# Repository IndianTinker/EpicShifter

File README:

This is a generic test board for using ULN2803 and 74HC595 Shift Registers.
Useful while testing LED Displays or getting used to new micros :D

It has seperate power pins for darlington and shiftregisters.

If you drive an LED Display using it. Use Shift Register for posiive drive
and ULN2803 for negative drive.

You may need to add pnp transistor for +ve side since the source limit on 595 
is less. In that case you have to invert logic as well.

Hope its useful

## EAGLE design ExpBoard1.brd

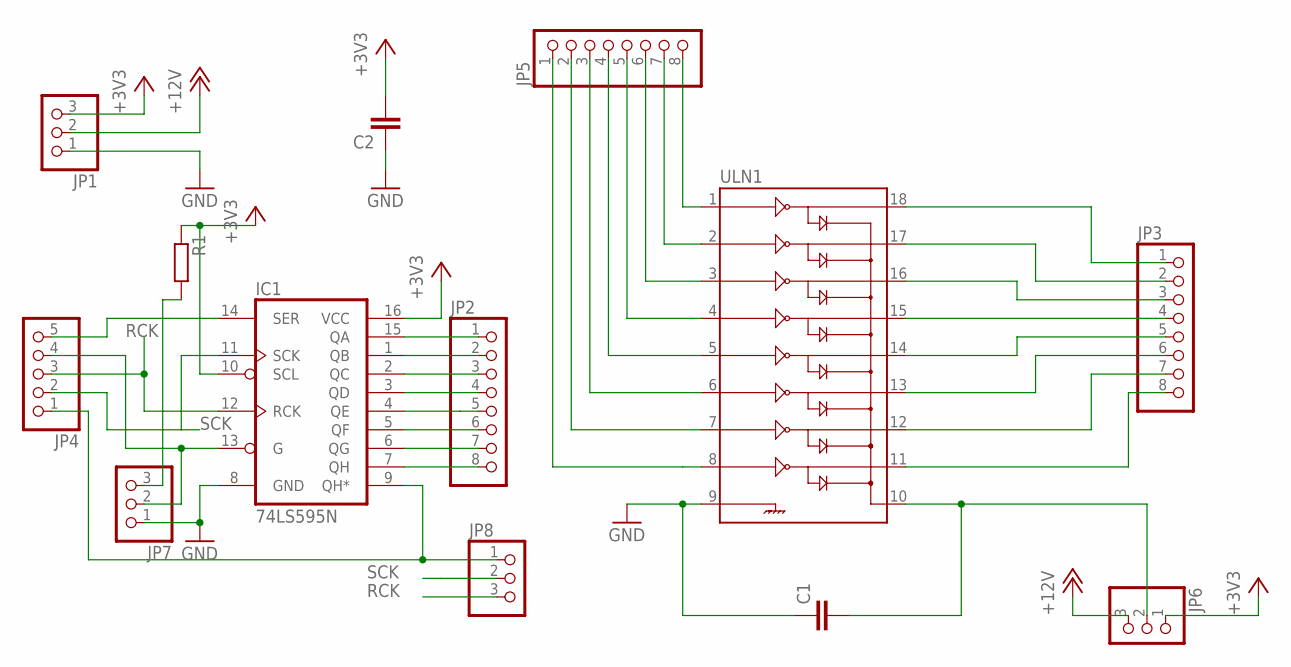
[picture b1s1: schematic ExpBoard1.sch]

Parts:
C1: C-EU050-024X044; C050-024X044
C2: C-EU025-024X044; C025-024X044
IC1: 74LS595N; DIL16
JP1, JP6, JP7, JP8: PINHD-1X3; 1X03
JP2, JP3, JP5: PINHD-1X8; 1X08
JP4: PINHD-1X5; 1X05
R1: R-EU_0207/12; 0207/12
ULN1: ULN2803DIP; DIL18

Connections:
+3V3: C2.2, IC1.10 (SCL), IC1.16 (VCC), JP1.3, JP6.1, R1.1
+12V: JP1.2, JP6.3
GND: C1.1, C2.1, IC1.8 (GND), JP1.1, JP7.1, ULN1.9
unnamed: IC1.14 (SER), JP4.5
unnamed: C1.2, JP6.2, ULN1.10
unnamed: JP3.1, ULN1.18
unnamed: JP3.2, ULN1.17
unnamed: JP3.3, ULN1.16
unnamed: JP3.4, ULN1.15
unnamed: JP3.5, ULN1.14
unnamed: JP3.6, ULN1.13
unnamed: JP3.7, ULN1.12
unnamed: JP3.8, ULN1.11
unnamed: JP5.8, ULN1.1
unnamed: JP5.7, ULN1.2
unnamed: JP5.6, ULN1.3
unnamed: JP5.5, ULN1.4
unnamed: JP5.4, ULN1.5
unnamed: JP5.3, ULN1.6
unnamed: JP5.2, ULN1.7
unnamed: JP5.1, ULN1.8
unnamed: IC1.15 (QA), JP2.1
unnamed: IC1.1 (QB), JP2.2
unnamed: IC1.2 (QC), JP2.3
unnamed: IC1.3 (QD), JP2.4
unnamed: IC1.4 (QE), JP2.5
unnamed: IC1.5 (QF), JP2.6
unnamed: IC1.6 (QG), JP2.7
unnamed: IC1.7 (QH), JP2.8
unnamed: IC1.13 (G), JP4.4, JP7.2
unnamed: IC1.9 (QH*), JP4.1, JP8.1
unnamed: JP7.3, R1.2
RCK: IC1.12 (RCK), JP4.3, JP8.3
SCK: IC1.11 (SCK), JP4.2, JP8.2

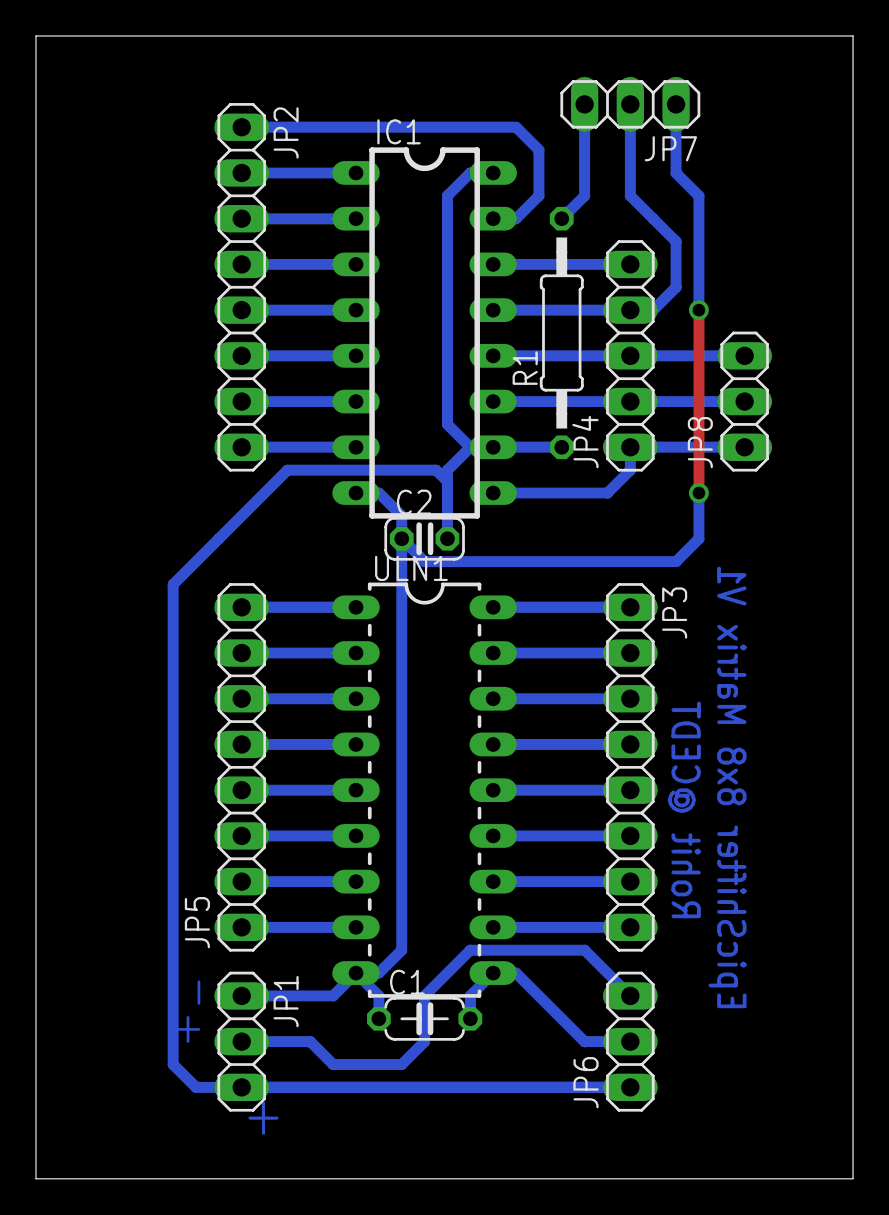
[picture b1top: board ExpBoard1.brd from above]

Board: 2 copper layers, 45.4 x 63.5 mm, 13 parts (0 on the bottom side), 34 nets.

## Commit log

2014-03-12 All Files added
2014-03-12 Added Screw mounts
2014-03-12 modified the readme

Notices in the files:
parts and their libraries:
SparkFun: Licensing: CC v3.0 Share-Alike You are welcome to use this library for commercial purposes.
